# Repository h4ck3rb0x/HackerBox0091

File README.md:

# HackerBox 0091: Fibonacci

[HackerBox 0091 Product Page](https://hackerboxes.com/products/hackerbox-0091-fibonacci)

[HackerBox 0091 Official Online Guide](https://www.instructables.com/HackerBox-0091-Fibonacci/)

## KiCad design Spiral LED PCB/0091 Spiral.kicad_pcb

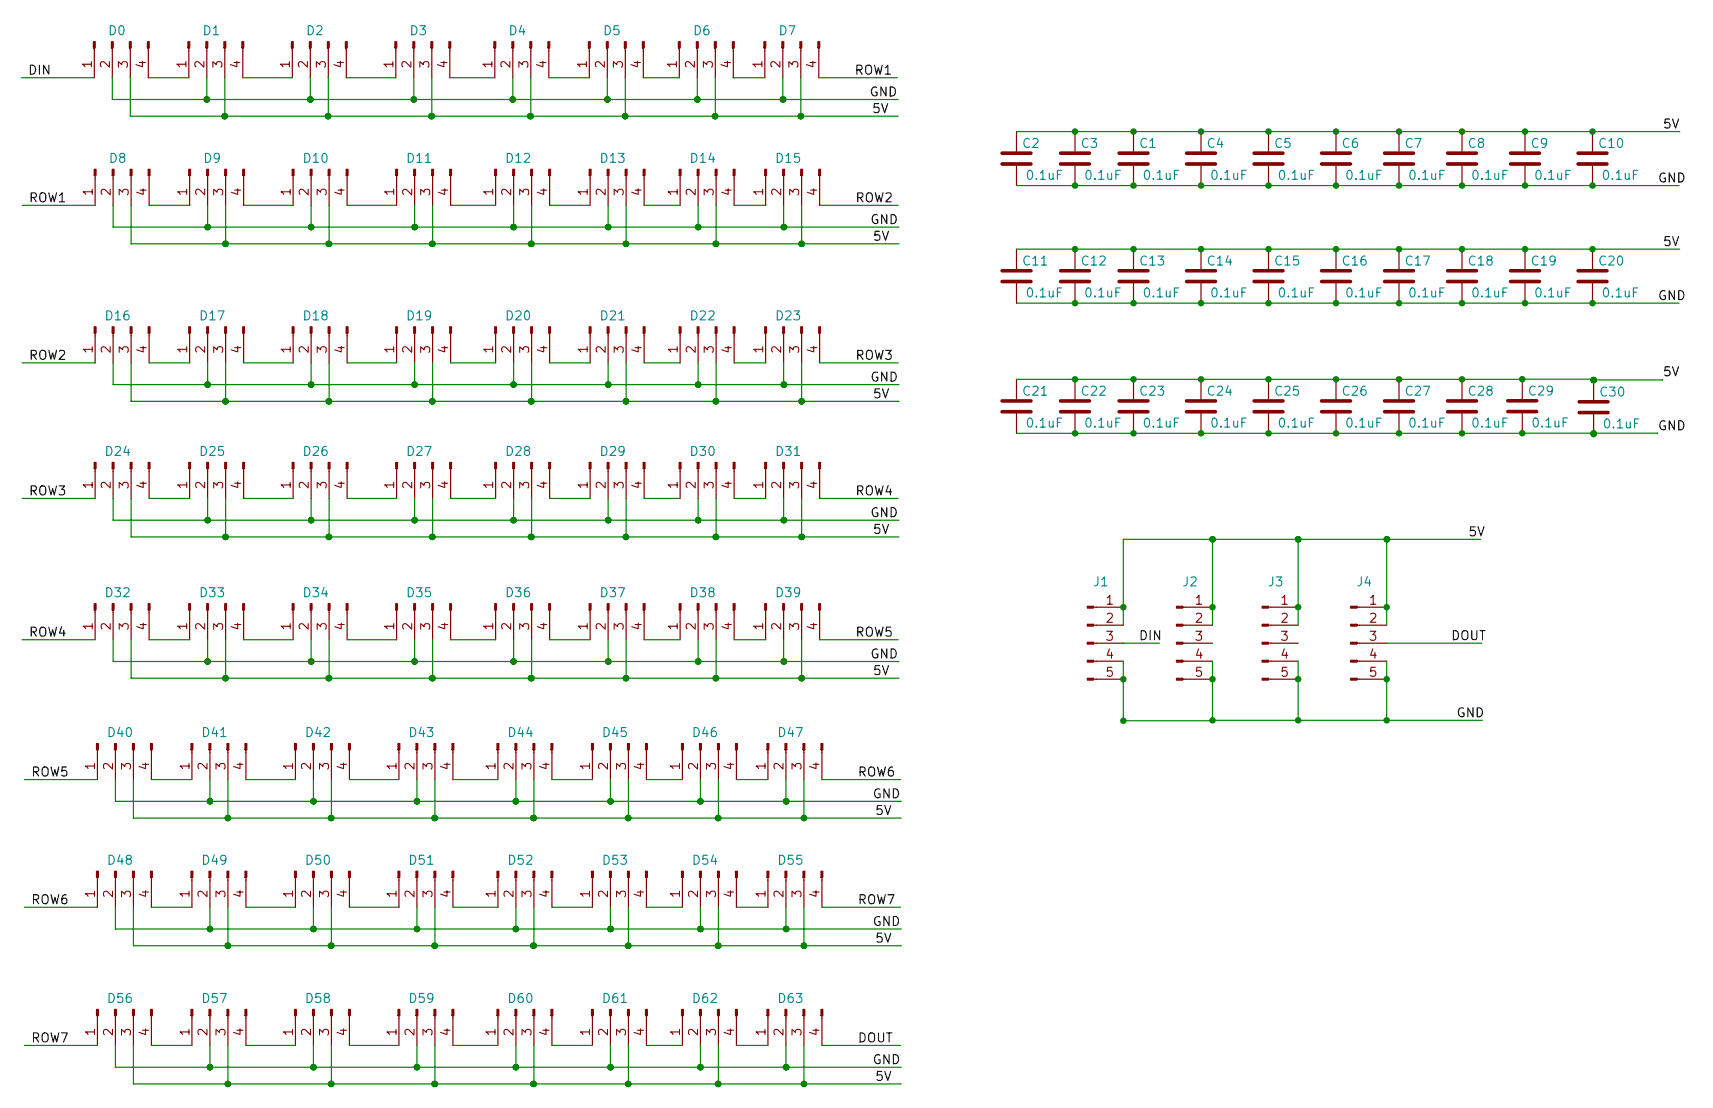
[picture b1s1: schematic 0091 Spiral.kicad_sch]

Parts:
C1, C2, C3, C4, C5, C6, C7, C8, C9, C10, C11, C12, C13, C14, C15, C16, C17, C18, C19, C20, C21, C22, C23, C24, C25, C26, C27, C28, C29, C30: 0.1uF; C_1210_3225Metric_Pad1.33x2.70mm_HandSolder
D0, D1, D2, D3, D4, D5, D6, D7, D8, D9, D10, D11, D12, D13, D14, D15, D16, D17, D18, D19, D20, D21, D22, D23, D24, D25, D26, D27, D28, D29, D30, D31, D32, D33, D34, D35, D36, D37, D38, D39, D40, D41, D42, D43, D44, D45, D46, D47, D48, D49, D50, D51, D52, D53, D54, D55, D56, D57, D58, D59, D60, D61, D62, D63: Conn_01x04_Male; LED_D5.0mm-4_RGB
J1, J2, J3, J4: Conn_01x05_Male; PinHeader_1x05_P2.54mm_Vertical

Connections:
/5V: C1.1, C2.1, C3.1, C4.1, C5.1, C6.1, C7.1, C8.1, C9.1, C10.1, C11.1, C12.1, C13.1, C14.1, C15.1, C16.1, C17.1, C18.1, C19.1, C20.1, C21.1, C22.1, C23.1, C24.1, C25.1, C26.1, C27.1, C28.1, C29.1, C30.1, D0.3, D1.3, D2.3, D3.3, D4.3, D5.3, D6.3, D7.3, D8.3, D9.3, D10.3, D11.3, D12.3, D13.3, D14.3, D15.3, D16.3, D17.3, D18.3, D19.3, D20.3, D21.3, D22.3, D23.3, D24.3, D25.3, D26.3, D27.3, D28.3, D29.3, D30.3, D31.3, D32.3, D33.3, D34.3, D35.3, D36.3, D37.3, D38.3, D39.3, D40.3, D41.3, D42.3, D43.3, D44.3, D45.3, D46.3, D47.3, D48.3, D49.3, D50.3, D51.3, D52.3, D53.3, D54.3, D55.3, D56.3, D57.3, D58.3, D59.3, D60.3, D61.3, D62.3, D63.3, J1.1, J1.2, J2.1, J2.2, J3.1, J3.2, J4.1, J4.2
/DIN: D0.1, J1.3
/DOUT: D63.4, J4.3
/GND: C1.2, C2.2, C3.2, C4.2, C5.2, C6.2, C7.2, C8.2, C9.2, C10.2, C11.2, C12.2, C13.2, C14.2, C15.2, C16.2, C17.2, C18.2, C19.2, C20.2, C21.2, C22.2, C23.2, C24.2, C25.2, C26.2, C27.2, C28.2, C29.2, C30.2, D0.2, D1.2, D2.2, D3.2, D4.2, D5.2, D6.2, D7.2, D8.2, D9.2, D10.2, D11.2, D12.2, D13.2, D14.2, D15.2, D16.2, D17.2, D18.2, D19.2, D20.2, D21.2, D22.2, D23.2, D24.2, D25.2, D26.2, D27.2, D28.2, D29.2, D30.2, D31.2, D32.2, D33.2, D34.2, D35.2, D36.2, D37.2, D38.2, D39.2, D40.2, D41.2, D42.2, D43.2, D44.2, D45.2, D46.2, D47.2, D48.2, D49.2, D50.2, D51.2, D52.2, D53.2, D54.2, D55.2, D56.2, D57.2, D58.2, D59.2, D60.2, D61.2, D62.2, D63.2, J1.4, J1.5, J2.4, J2.5, J3.4, J3.5, J4.4, J4.5
/ROW1: D7.4, D8.1
/ROW2: D15.4, D16.1
/ROW3: D23.4, D24.1
/ROW4: D31.4, D32.1
/ROW5: D39.4, D40.1
/ROW6: D47.4, D48.1
/ROW7: D55.4, D56.1
unnamed: D0.4, D1.1
unnamed: D1.4, D2.1
unnamed: D2.4, D3.1
unnamed: D3.4, D4.1
unnamed: D4.4, D5.1
unnamed: D5.4, D6.1
unnamed: D6.4, D7.1
unnamed: D8.4, D9.1
unnamed: D9.4, D10.1
unnamed: D10.4, D11.1
unnamed: D11.4, D12.1
unnamed: D12.4, D13.1
unnamed: D13.4, D14.1
unnamed: D14.4, D15.1
unnamed: D16.4, D17.1
unnamed: D17.4, D18.1
unnamed: D18.4, D19.1
unnamed: D19.4, D20.1
unnamed: D20.4, D21.1
unnamed: D21.4, D22.1
unnamed: D22.4, D23.1
unnamed: D24.4, D25.1
unnamed: D25.4, D26.1
unnamed: D26.4, D27.1
unnamed: D27.4, D28.1
unnamed: D28.4, D29.1
unnamed: D29.4, D30.1
unnamed: D30.4, D31.1
unnamed: D32.4, D33.1
unnamed: D33.4, D34.1
unnamed: D34.4, D35.1
unnamed: D35.4, D36.1
unnamed: D36.4, D37.1
unnamed: D37.4, D38.1
unnamed: D38.4, D39.1
unnamed: D40.4, D41.1
unnamed: D41.4, D42.1
unnamed: D42.4, D43.1
unnamed: D43.4, D44.1
unnamed: D44.4, D45.1
unnamed: D45.4, D46.1
unnamed: D46.4, D47.1
unnamed: D48.4, D49.1
unnamed: D49.4, D50.1
unnamed: D50.4, D51.1
unnamed: D51.4, D52.1
unnamed: D52.4, D53.1
unnamed: D53.4, D54.1
unnamed: D54.4, D55.1
unnamed: D56.4, D57.1
unnamed: D57.4, D58.1
unnamed: D58.4, D59.1
unnamed: D59.4, D60.1
unnamed: D60.4, D61.1
unnamed: D61.4, D62.1
unnamed: D62.4, D63.1

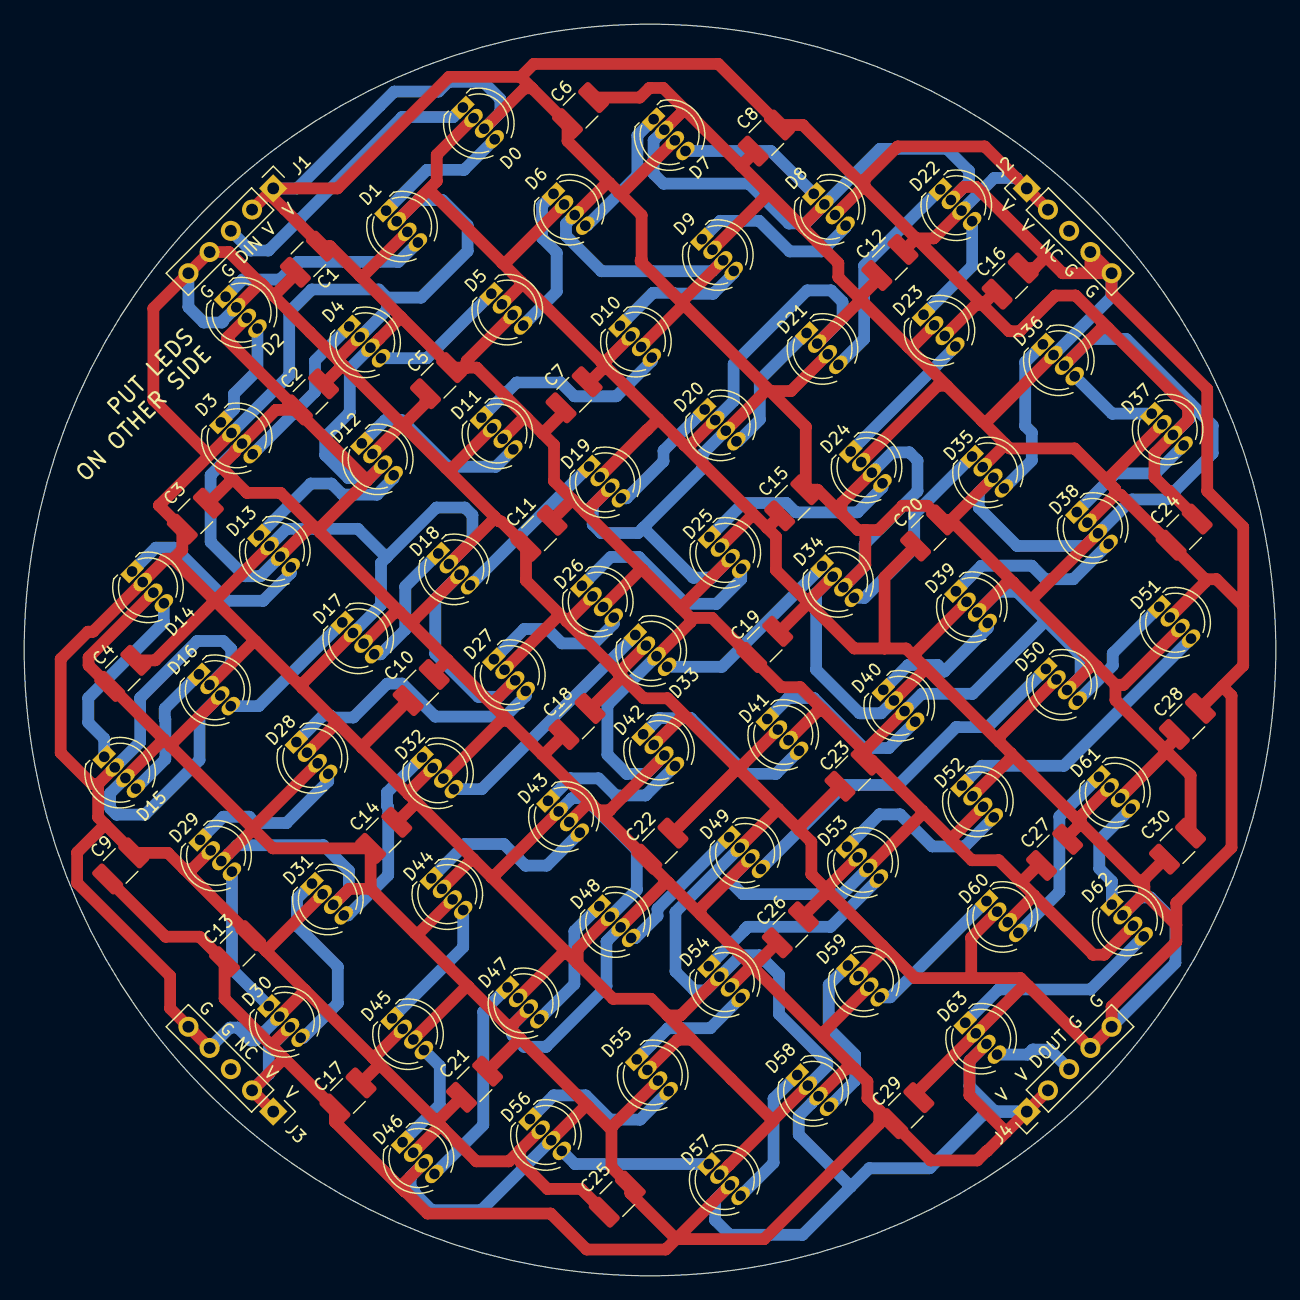
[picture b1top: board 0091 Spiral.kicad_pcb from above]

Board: 2 copper layers, 106.0 x 106.0 mm, 98 parts (0 on the bottom side), 67 nets.

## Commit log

2023-05-22 Rename 0091 Spiral.kicad_pcb to Spiral LED PCB/0091 Spiral.kicad_pcb
2023-05-22 Rename 0091 Spiral Backer.kicad_sch to Spiral LED Badge PCB/0091 Spiral Backer.kicad_sch
2023-05-23 Rename README to README.md
2023-06-14 Create LICENSE. txt
2023-06-14 Create LICENSE
